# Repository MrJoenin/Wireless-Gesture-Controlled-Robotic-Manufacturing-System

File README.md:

# 🦾 Wireless Gesture-Controlled Robotic Manufacturing System

A 6-DOF robotic arm controlled wirelessly in real-time using hand gestures captured by an MPU6050 IMU and transmitted via RF communication.

---

## 📸 Demo

🎥 [Watch Full Demo Video](https://drive.google.com/drive/folders/1Te0tW6EEjBbD6eXdm4avNDmqE-6lIaKK?usp=drive_link)

---

## 🔍 Overview

This system allows an operator to control a robotic arm simply by moving their hand. An **MPU6050 gyroscope/accelerometer** captures wrist orientation and transmits motion data wirelessly via **RF modules** to a receiver Arduino that drives **6 servo motors** — one per joint. An **ultrasonic sensor** detects nearby objects and triggers a **buzzer** as a proximity alert.

This project was built as a group capstone for **ECET-230-001**, covering embedded systems, wireless communication, PCB design, and mechanical design end-to-end.

---

## ✨ Features

- Real-time wireless gesture control via MPU6050 IMU (pitch, roll, yaw)
- 6 degrees of freedom — base, shoulder, elbow, wrist pitch, wrist roll, gripper
- RF 433MHz communication between handheld controller and arm
- Ultrasonic proximity detection with piezo buzzer audio alert
- LCD display for live system status feedback
- Custom PCB designed in KiCad
- 3D printed mechanical structure (PLA+ / PETG)
- Full project documentation: schematics, logs, test plans, CAD files

---

## ⚙️ Hardware Components

| Component | Quantity | Purpose |
|---|---|---|
| Arduino Uno | 2 | Transmitter & Receiver microcontrollers |
| MPU6050 IMU | 1 | Captures hand orientation (I2C) |
| RF Transmitter + Receiver (433MHz) | 1 pair | Wireless data link |
| Servo Motors | 6 | Drives each joint of the arm |
| Ultrasonic Sensor (HC-SR04) | 2 | Object/proximity detection |
| Piezo Buzzer | 1 | Audio proximity alert |
| LCD Display (I2C) | 1 | Live system status |
| Push Buttons | 5 | Manual input controls |
| LEDs (Red & Green) | 2 | Status indicators |
| 9V Battery + Battery Pack | 1 | Portable power supply |
| Custom PCB (KiCad) | 1 | Clean circuit integration |

**Estimated Total Cost: Under $150**

---

## 🧠 How It Works

```
[ Hand Movement ]
       ↓
[ MPU6050 reads pitch / roll / yaw ]
       ↓
[ Transmitter Arduino encodes data + sends via RF ]
       ↓
[ Receiver Arduino decodes signal ]
       ↓
[ 6 Servo motors move to matching joint angles ]
       ↓
[ Ultrasonic sensor monitors proximity → Buzzer alert ]
```

---

## 🛠️ Tools & Technologies

| Category | Tools |
|---|---|
| Programming | Arduino IDE (C/C++) |
| Mechanical Design | SolidWorks / Fusion 360 |
| PCB Design | KiCad |
| Manufacturing | 3D Printing (PLA+ / PETG), Laser Cutting |
| Version Control | GitHub |
| Libraries | `Wire.h`, `MPU6050.h`, `VirtualWire`, `Servo.h`, `LiquidCrystal_I2C.h` |

---

## 📁 Repository Structure

```
Wireless-Gesture-Controlled-Robotic-Manufacturing-System/
├── Software/           # Arduino .ino source files (transmitter & receiver)
├── Design/             # System architecture, block diagrams, circuit schematics
├── PCB Files/          # KiCad PCB design files
├── Robot 3D Model/     # SolidWorks / Fusion 360 CAD files
├── Logs/               # Weekly progress logs
├── Tasks/              # Task tracking and completion status
├── Definitions/        # Official project scope and requirements
├── Proof of Concept.md # Early validation and feasibility notes
├── Testing Document.md # Test cases, results, and validation
├── LICENSE
└── README.md
```

---

## 🚀 Getting Started

### Prerequisites
- Arduino IDE installed
- Required libraries (install via Library Manager):
  - `MPU6050` by Electronic Cats
  - `VirtualWire` or `RadioHead` for RF
  - `LiquidCrystal_I2C` for LCD
  - `Servo` (built-in)

### Upload Steps

1. Clone this repo:
   ```bash
   git clone https://github.com/MrJoenin/Wireless-Gesture-Controlled-Robotic-Manufacturing-System.git
   ```
2. Open `Software/transmitter.ino` → upload to the **controller Arduino** (with MPU6050)
3. Open `Software/receiver.ino` → upload to the **arm Arduino**
4. Power both units — the arm will mirror hand movements in real time

---

## 📆 Project Timeline

| Phase | Duration | Description |
|---|---|---|
| Research & Planning | Weeks 1–2 | Brainstorm, block diagram, parts research |
| Design & Prototyping | Weeks 3–6 | CAD models, circuit design, PCB layout |
| Implementation | Weeks 7–10 | Build prototype, write firmware |
| Testing & Debugging | Weeks 11–12 | Verify requirements, fix issues |
| Final Delivery | Week 13 | Report, presentation, live demo |

---

## 🧩 Challenges & What We Learned

- **Servo power management** — Powering all 6 servos from the Arduino caused brownouts. Fixed by using a dedicated external supply with a shared ground.
- **RF signal reliability** — Raw RF is noisy; added basic packet validation to prevent erratic servo movement from corrupted signals.
- **IMU drift** — Raw gyroscope data drifts over time. Applied a complementary filter combining accelerometer + gyroscope data for stable, accurate readings.
- **PCB design iteration** — First PCB revision had routing issues; KiCad's DRC tool helped catch and fix them before fabrication.

---

## 🔮 Future Improvements

- [ ] Upgrade to nRF24L01 for bidirectional, more reliable communication
- [ ] Add inverse kinematics for coordinate-based positioning
- [ ] Implement a mobile app as an alternative controller
- [ ] Add force feedback on the gripper
- [ ] Update Receiver and Transmitter PCB

---

## 👥 Team

| Member | Role |
|---|---|
| John (MrJoenin) | CAD, Mechanical Design |
| Alicia | Coding, Testing & Validation |
| Larbi | Research, Schematics, PCB Design |

---

## 📄 License

This project is open source under the [MIT License](LICENSE).  
Feel free to use and modify with attribution.

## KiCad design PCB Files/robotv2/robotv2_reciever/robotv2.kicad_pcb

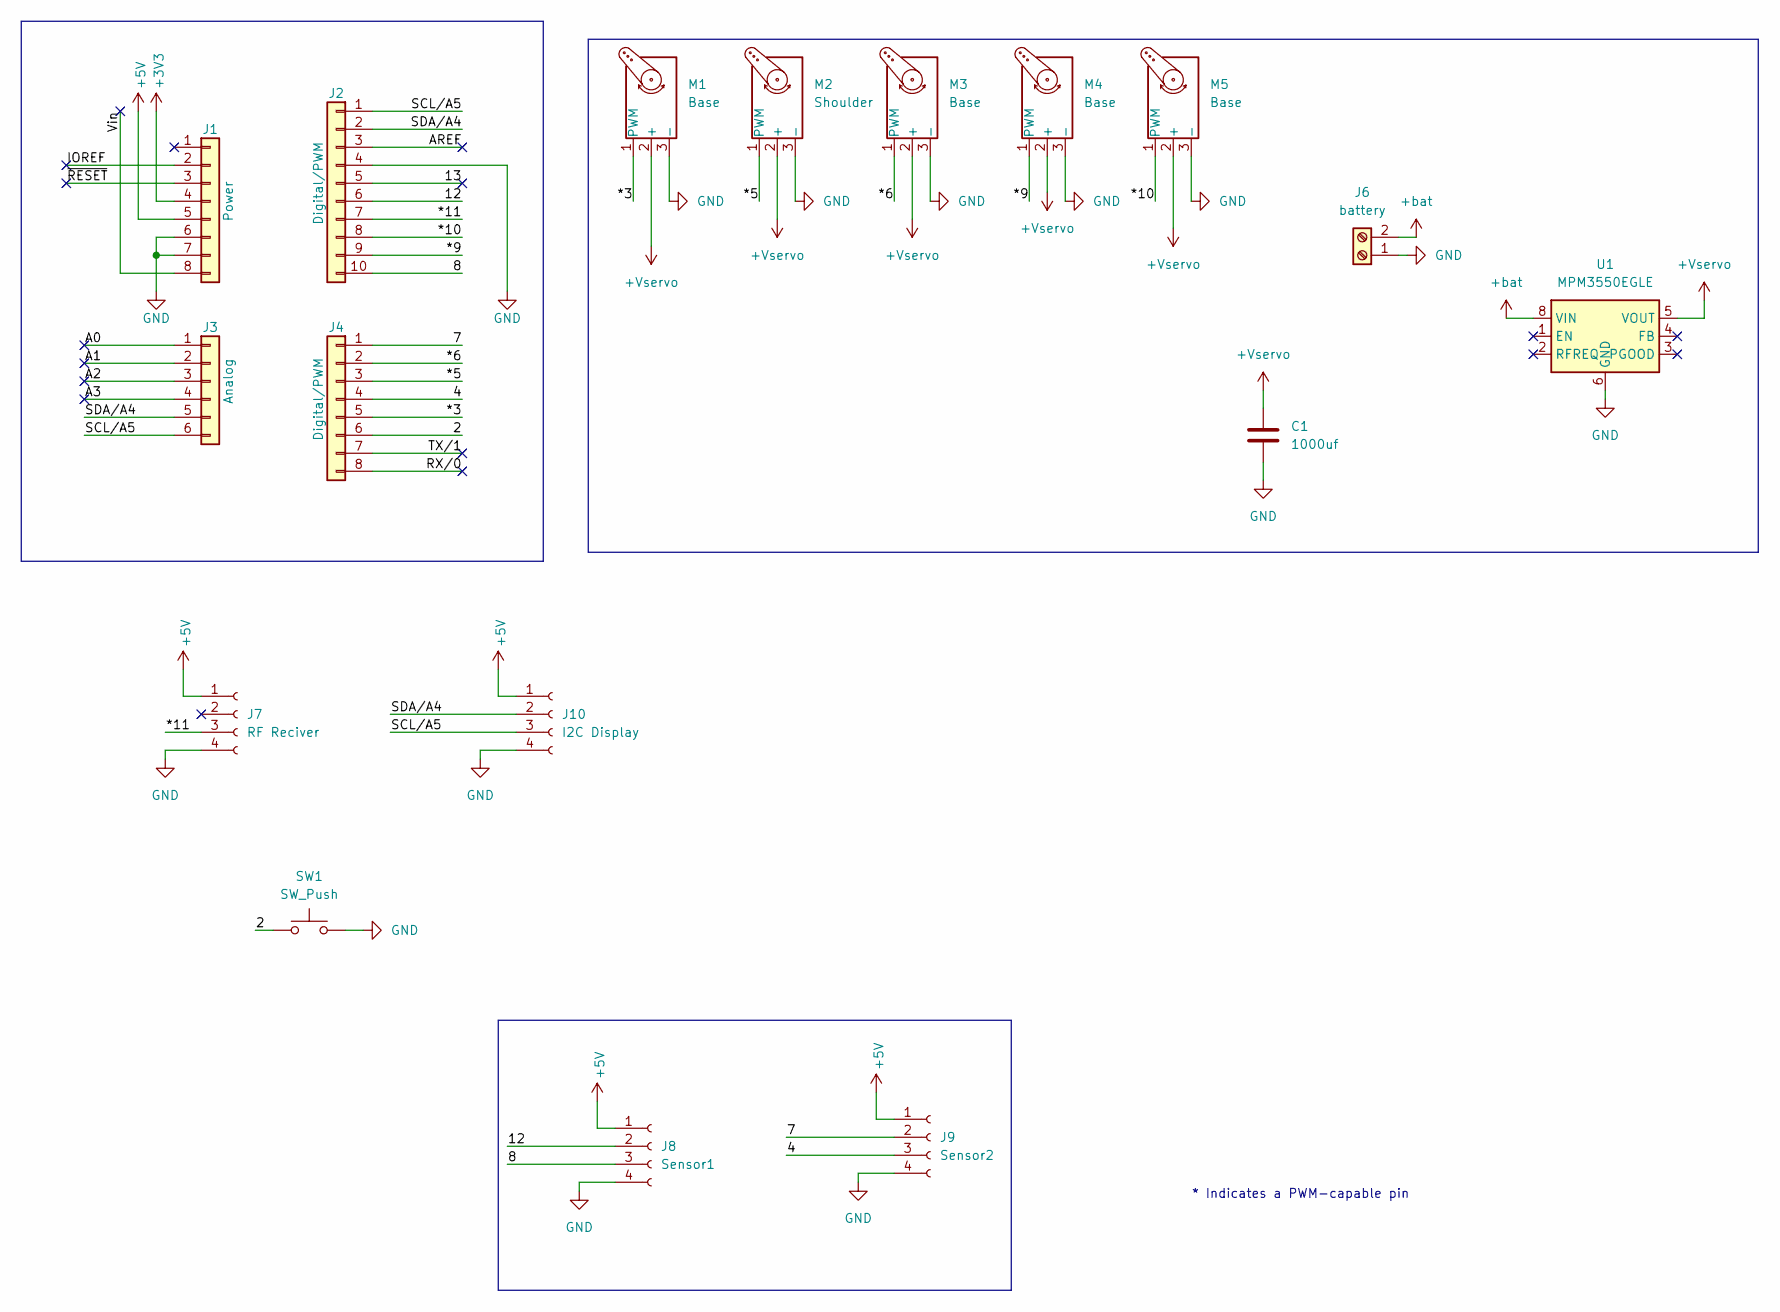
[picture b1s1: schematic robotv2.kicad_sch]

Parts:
C1: 1000uf; CP_Radial_D10.0mm_P2.50mm
J1: Power; PinSocket_1x08_P2.54mm_Vertical
J2: Digital/PWM; PinSocket_1x10_P2.54mm_Vertical
J3: Analog; PinSocket_1x06_P2.54mm_Vertical
J4: Digital/PWM; PinSocket_1x08_P2.54mm_Vertical
J6: battery; TerminalBlock_Phoenix_MKDS-1,5-2-5.08_1x02_P5.08mm_Horizont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
J7: RF Reciver; PinSocket_1x04_P2.54mm_Vertical
J8: Sensor1; PinSocket_1x04_P2.54mm_Vertical
J9: Sensor2; PinSocket_1x04_P2.54mm_Vertical
J10: I2C Display; PinSocket_1x04_P2.54mm_Vertical
M1, M3, M4, M5: Base; PinHeader_1x03_P2.54mm_Vertical
M2: Shoulder; PinHeader_1x03_P2.54mm_Vertical
SW1: SW_Push; SW_PUSH_6mm
U1: MPM3550EGLE; MPS_LGA-18-10EP_12x12mm_P3.3mm

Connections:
+3V3: J1.4
+5V: J1.5, J7.1, J8.1, J9.1, J10.1
+Vservo: C1.1, M1.2 (+), M2.2 (+), M3.2 (+), M4.2 (+), M5.2 (+), U1.5 (VOUT)
+bat: J6.2, U1.8 (VIN)
/2: J4.6, SW1.1
/4: J4.4, J9.3
/7: J4.1, J9.2
/8: J2.10, J8.3
/12: J2.6, J8.2
/13: J2.5
/*3: J4.5, M1.1 (PWM)
/*5: J4.3, M2.1 (PWM)
/*6: J4.2, M3.1 (PWM)
/*9: J2.9, M4.1 (PWM)
/*10: J2.8, M5.1 (PWM)
/*11: J2.7, J7.3
/A0: J3.1
/A1: J3.2
/A2: J3.3
/A3: J3.4
/AREF: J2.3
/IOREF: J1.2
/RX/0: J4.8
/SCL/A5: J2.1, J3.6, J10.3
/SDA/A4: J2.2, J3.5, J10.2
/TX/1: J4.7
/Vin: J1.8
/~RESET: J1.3
GND: C1.2, J1.6, J1.7, J2.4, J6.1, J7.4, J8.4, J9.4, J10.4, M1.3 (-), M2.3 (-), M3.3 (-), M4.3 (-), M5.3 (-), SW1.2, U1.6 (GND), U1.7 (GND), U1.9 (GND), U1.10 (GND), U1.11 (GND), U1.12 (GND), U1.13 (GND), U1.14 (GND), U1.15 (GND), U1.16 (GND), U1.17 (GND), U1.18 (GND)

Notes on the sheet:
* Indicates a PWM-capable pin

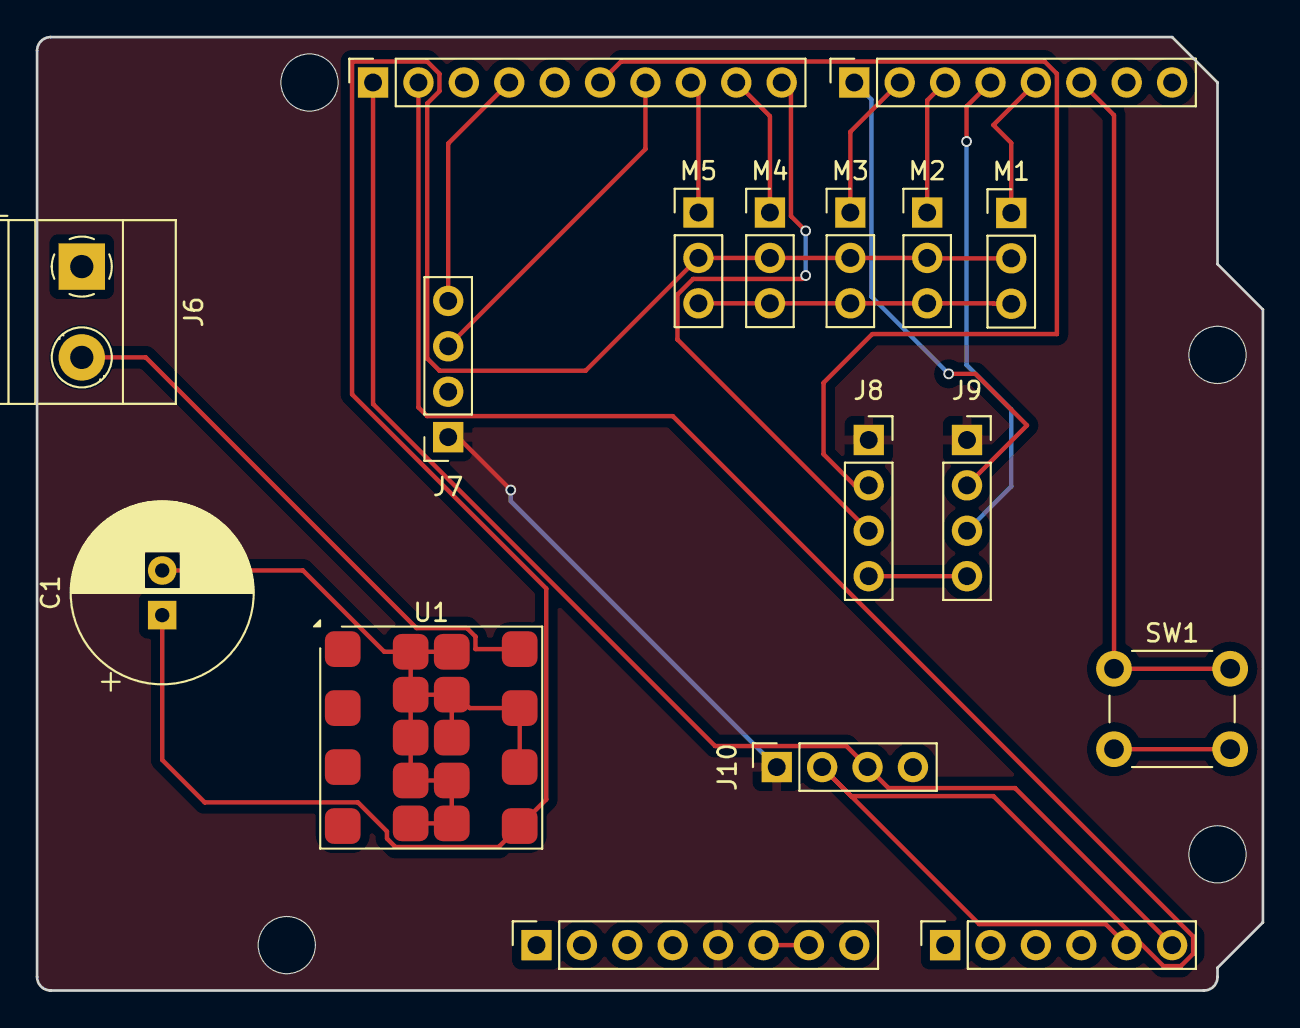
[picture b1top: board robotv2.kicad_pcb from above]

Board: 2 copper layers, 68.6 x 53.3 mm, 21 parts (0 on the bottom side), 17 nets.

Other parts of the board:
MH1, MH2, MH3, MH4: MountingHole_3.2mm

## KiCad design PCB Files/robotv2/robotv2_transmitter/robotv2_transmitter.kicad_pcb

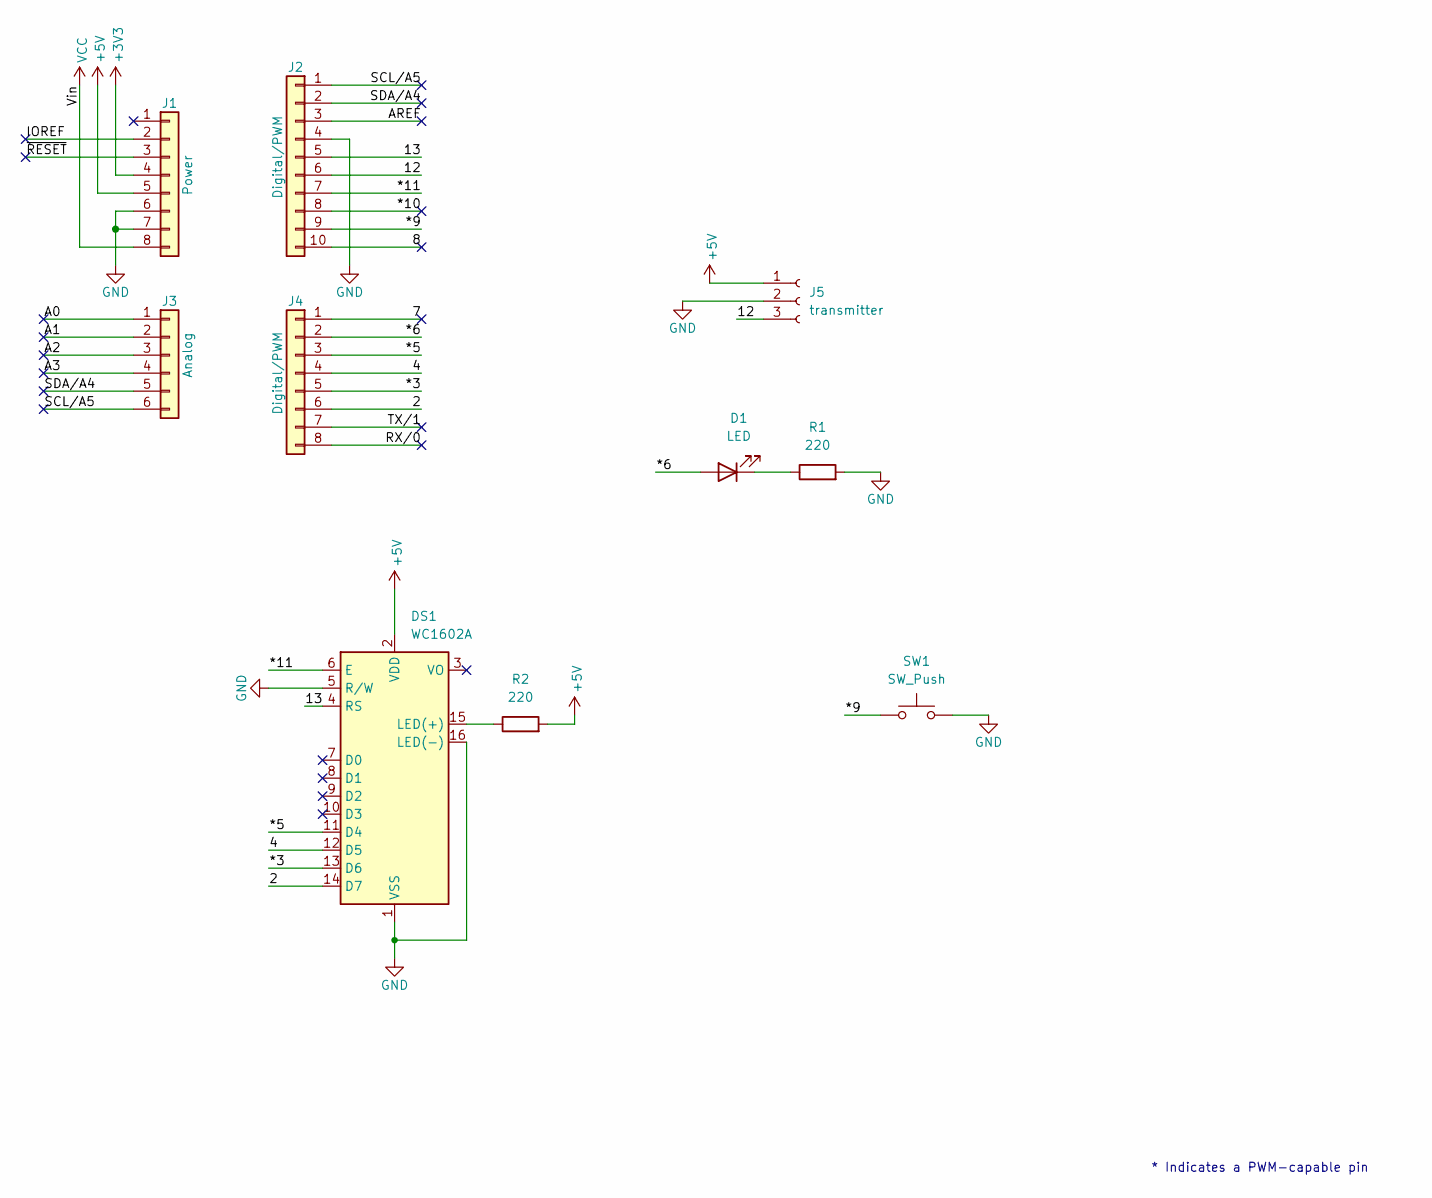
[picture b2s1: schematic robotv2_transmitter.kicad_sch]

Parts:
D1: LED; LED_D3.0mm
DS1: WC1602A; PinSocket_1x16_P2.54mm_Vertical
J1: Power; PinSocket_1x08_P2.54mm_Vertical
J2: Digital/PWM; PinSocket_1x10_P2.54mm_Vertical
J3: Analog; PinSocket_1x06_P2.54mm_Vertical
J4: Digital/PWM; PinSocket_1x08_P2.54mm_Vertical
J5: transmitter; PinSocket_1x03_P2.54mm_Vertical
R1, R2: 220; R_Axial_DIN0411_L9.9mm_D3.6mm_P12.70mm_Horizontal
SW1: SW_Push; SW_PUSH_6mm

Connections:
+3V3: J1.4
+5V: DS1.2 (VDD), J1.5, J5.1, R2.2
/2: DS1.14 (D7), J4.6
/4: DS1.12 (D5), J4.4
/7: J4.1
/8: J2.10
/12: J2.6, J5.3
/13: DS1.4 (RS), J2.5
/*3: DS1.13 (D6), J4.5
/*5: DS1.11 (D4), J4.3
/*6: D1.2 (A), J4.2
/*9: J2.9, SW1.1
/*10: J2.8
/*11: DS1.6 (E), J2.7
/A0: J3.1
/A1: J3.2
/A2: J3.3
/A3: J3.4
/AREF: J2.3
/IOREF: J1.2
/RX/0: J4.8
/SCL/A5: J2.1, J3.6
/SDA/A4: J2.2, J3.5
/TX/1: J4.7
/~RESET: J1.3
GND: DS1.1 (VSS), DS1.5 (R/W), DS1.16 (LED(-)), J1.6, J1.7, J2.4, J5.2, R1.2, SW1.2
unnamed: D1.1 (K), R1.1
unnamed: DS1.15 (LED(+)), R2.1
VCC: J1.8

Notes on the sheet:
* Indicates a PWM-capable pin

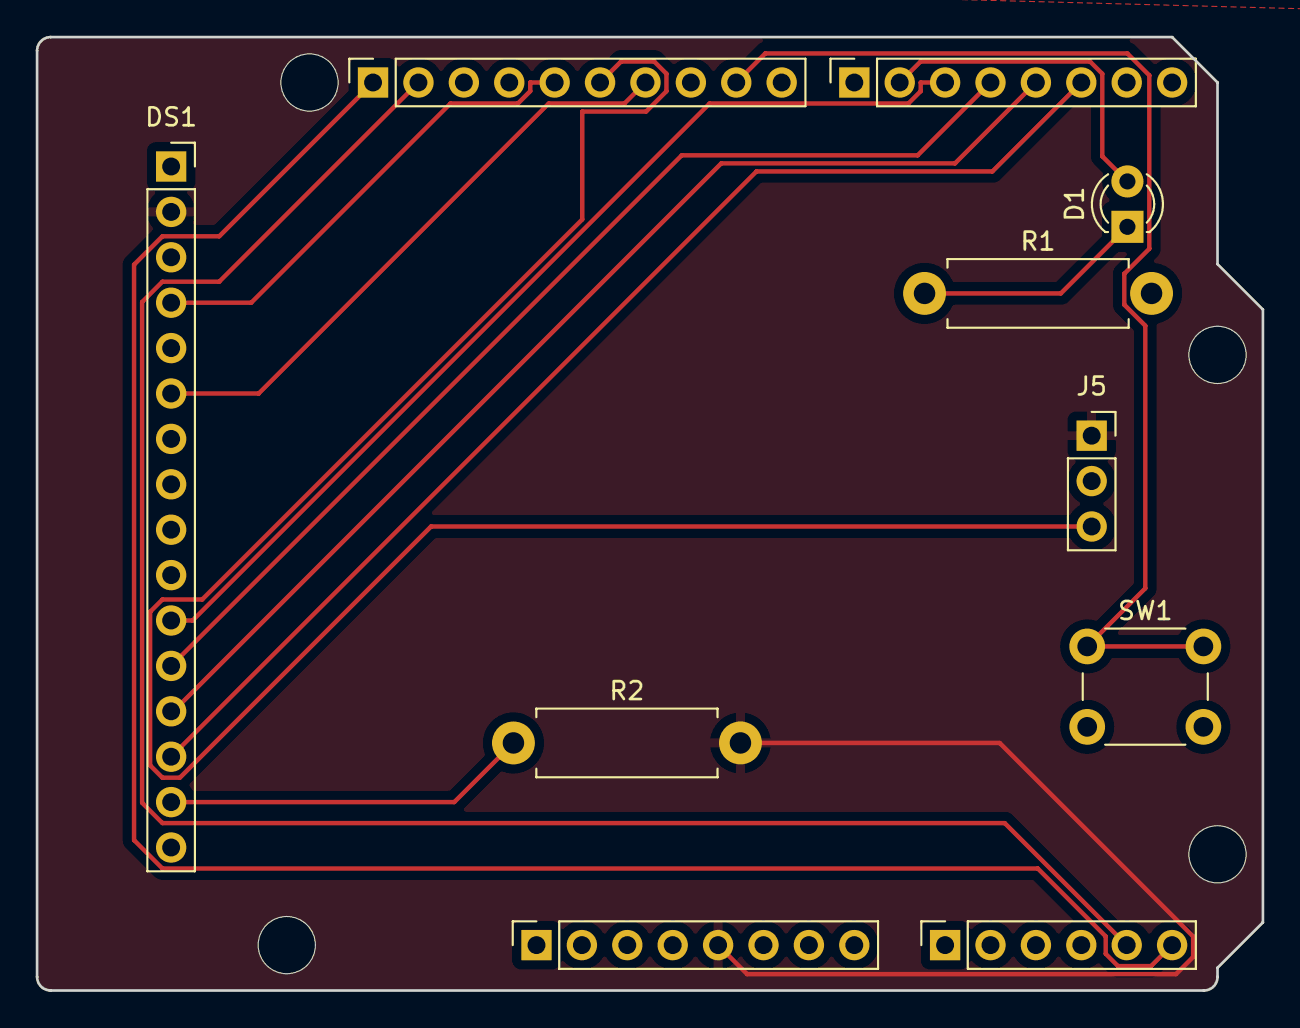
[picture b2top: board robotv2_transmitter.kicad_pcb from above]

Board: 2 copper layers, 68.6 x 53.3 mm, 14 parts (0 on the bottom side), 15 nets.

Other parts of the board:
MH1, MH2, MH3, MH4: MountingHole_3.2mm

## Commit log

2026-02-24 Update team member roles and usage instructions
    Corrected punctuation and added a new step for software access.
2026-03-08 Revise README with project overview and features
    Expanded project details, features, and team roles in README.
2026-03-08 Update project title from 5DOF to 6DOF robot
2026-03-08 Add demo section with image placeholder
    Added a demo section with an image placeholder in the README.
2026-03-08 Update demo section in README
    Removed placeholder text for demo image in README.
2026-03-08 Remove demo link from README
    Removed demo link from README.
2026-03-08 Add demo image for robotic arm
    Added an image of the Wireless Gesture-Controlled Robotic Arm to the demo section.
2026-03-08 Add demo image to README
    Added an additional demo image to the README.
2026-03-08 Fix image path and update demo in README
    Correct the image path and update demo image.
2026-03-08 Clean up README by removing extra image tag
    Removed unnecessary image tag from README.
2026-03-08 Add demo video link to README
2026-03-08 Fix demo video link formatting in README
2026-03-08 Fix link formatting for demo video in README
2026-03-11 Fix HTML entities in README description
    Removed unnecessary HTML entities from the description.
2026-03-11 Fix typo in servo power management description
    Corrected a typo in the servo power management section of the README.
